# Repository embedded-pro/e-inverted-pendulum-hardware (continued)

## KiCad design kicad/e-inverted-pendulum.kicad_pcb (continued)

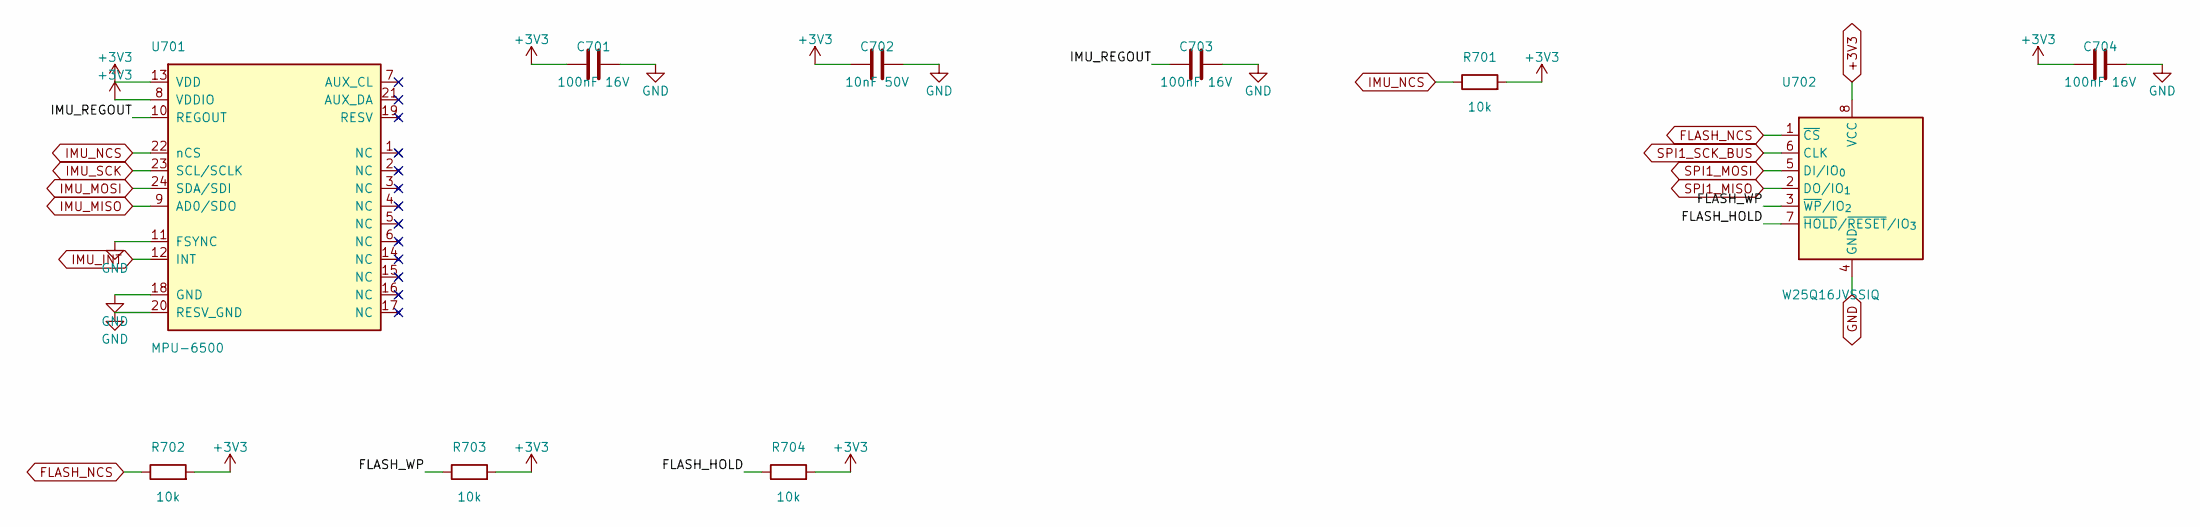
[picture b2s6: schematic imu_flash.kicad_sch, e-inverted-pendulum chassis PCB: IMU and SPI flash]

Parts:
C701, C703, C704: 100nF 16V; C_0402_1005Metric; MPN CL05B104KO5NNNC; LCSC C1525
C702: 10nF 50V; C_0603_1608Metric; MPN CL10B103KB8NNNC; LCSC C1589
R701, R702, R703, R704: 10k; R_0603_1608Metric; MPN 0603WAF1002T5E; LCSC C25804
U701: MPU-6500; InvenSense_QFN-24_3x3mm_P0.4mm; MPN MPU-6500; LCSC C50278
U702: W25Q16JVSSIQ; SOIC-8_5.3x5.3mm_P1.27mm; MPN W25Q16JVSSIQ; LCSC C131025

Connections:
+3V3: C701.1, C702.1, C704.1, R701.2, R702.2, R703.2, R704.2, U701.8 (VDDIO), U701.13 (VDD), U702.8 (VCC); also elsewhere on the board
/7 IMU and SPI flash/FLASH_HOLD: R704.1, U702.7 (~HOLD/~RESET/IO_{3})
/7 IMU and SPI flash/FLASH_WP: R703.1, U702.3 (~WP/IO_{2})
/7 IMU and SPI flash/IMU_REGOUT: C703.1, U701.10 (REGOUT)
FLASH_NCS: R702.1, U702.1 (~CS); also elsewhere on the board
GND: C701.2, C702.2, C703.2, C704.2, U701.11 (FSYNC), U701.18 (GND), U701.20 (RESV_GND), U702.4 (GND); also elsewhere on the board
IMU_INT: U701.12 (INT); also elsewhere on the board
IMU_MISO: U701.9 (AD0/SDO); also elsewhere on the board
IMU_MOSI: U701.24 (SDA/SDI); also elsewhere on the board
IMU_NCS: R701.1, U701.22 (nCS); also elsewhere on the board
IMU_SCK: U701.23 (SCL/SCLK); also elsewhere on the board
SPI1_MISO: U702.2 (DO/IO_{1}); also elsewhere on the board
SPI1_MOSI: U702.5 (DI/IO_{0}); also elsewhere on the board
SPI1_SCK_BUS: U702.6 (CLK); also elsewhere on the board

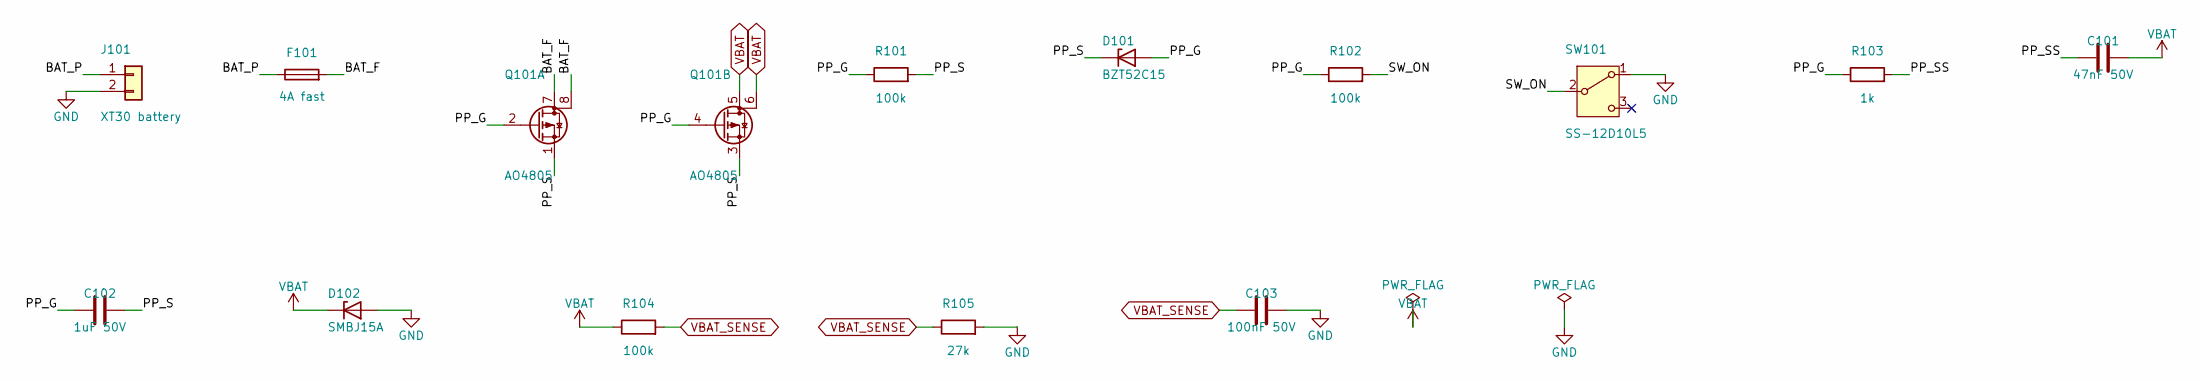
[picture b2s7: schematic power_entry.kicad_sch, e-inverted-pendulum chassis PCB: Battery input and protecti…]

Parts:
C101: 47nF 50V; C_0603_1608Metric; MPN CL10B473KB8NNNC; LCSC C1622
C102: 1uF 50V; C_0603_1608Metric; MPN CL10A105KB8NNNC; LCSC C15849
C103: 100nF 50V; C_0603_1608Metric; MPN CC0603KRX7R9BB104; LCSC C14663
D101: BZT52C15; D_SOD-123; MPN BZT52C15; LCSC C2104
D102: SMBJ15A; D_SMB; MPN SMBJ15A; LCSC C83846
F101: 4A fast; Fuse_1206_3216Metric; MPN 1206FA-4A; LCSC C2937379
J101: XT30 battery; AMASS_XT30UPB-F_1x02_P5.00mm_Vertical; MPN XT30UPB-F30.G.Y; LCSC C108769
Q101: AO4805; SOIC-8_3.9x4.9mm_P1.27mm; MPN AO4805; LCSC C3040596
R101, R102, R104: 100k; R_0603_1608Metric; MPN 0603WAF1003T5E; LCSC C25803
R103: 1k; R_0603_1608Metric; MPN 0603WAF1001T5E; LCSC C21190
R105: 27k; R_0603_1608Metric; MPN 0603WAF2702T5E; LCSC C22967
SW101: SS-12D10L5; SW_Slide_SPDT_SS-12D10L5_P4.70mm; MPN SS-12D10L5; LCSC C319012

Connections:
/1 Battery input and protection/BAT_F: F101.2, Q101.7 (D), Q101.8 (D)
/1 Battery input and protection/BAT_P: F101.1, J101.1
/1 Battery input and protection/PP_G: C102.1, D101.2 (A), Q101.2 (G), Q101.4 (G), R101.1, R102.1, R103.1
/1 Battery input and protection/PP_S: C102.2, D101.1 (K), Q101.1 (S), Q101.3 (S), R101.2
/1 Battery input and protection/PP_SS: C101.1, R103.2
/1 Battery input and protection/SW_ON: R102.2, SW101.2 (B)
GND: C103.2, D102.2 (A), J101.2, R105.2, SW101.1 (A); also elsewhere on the board
VBAT: C101.2, D102.1 (K), Q101.5 (D), Q101.6 (D), R104.1; also elsewhere on the board
VBAT_SENSE: C103.1, R104.2, R105.1; also elsewhere on the board

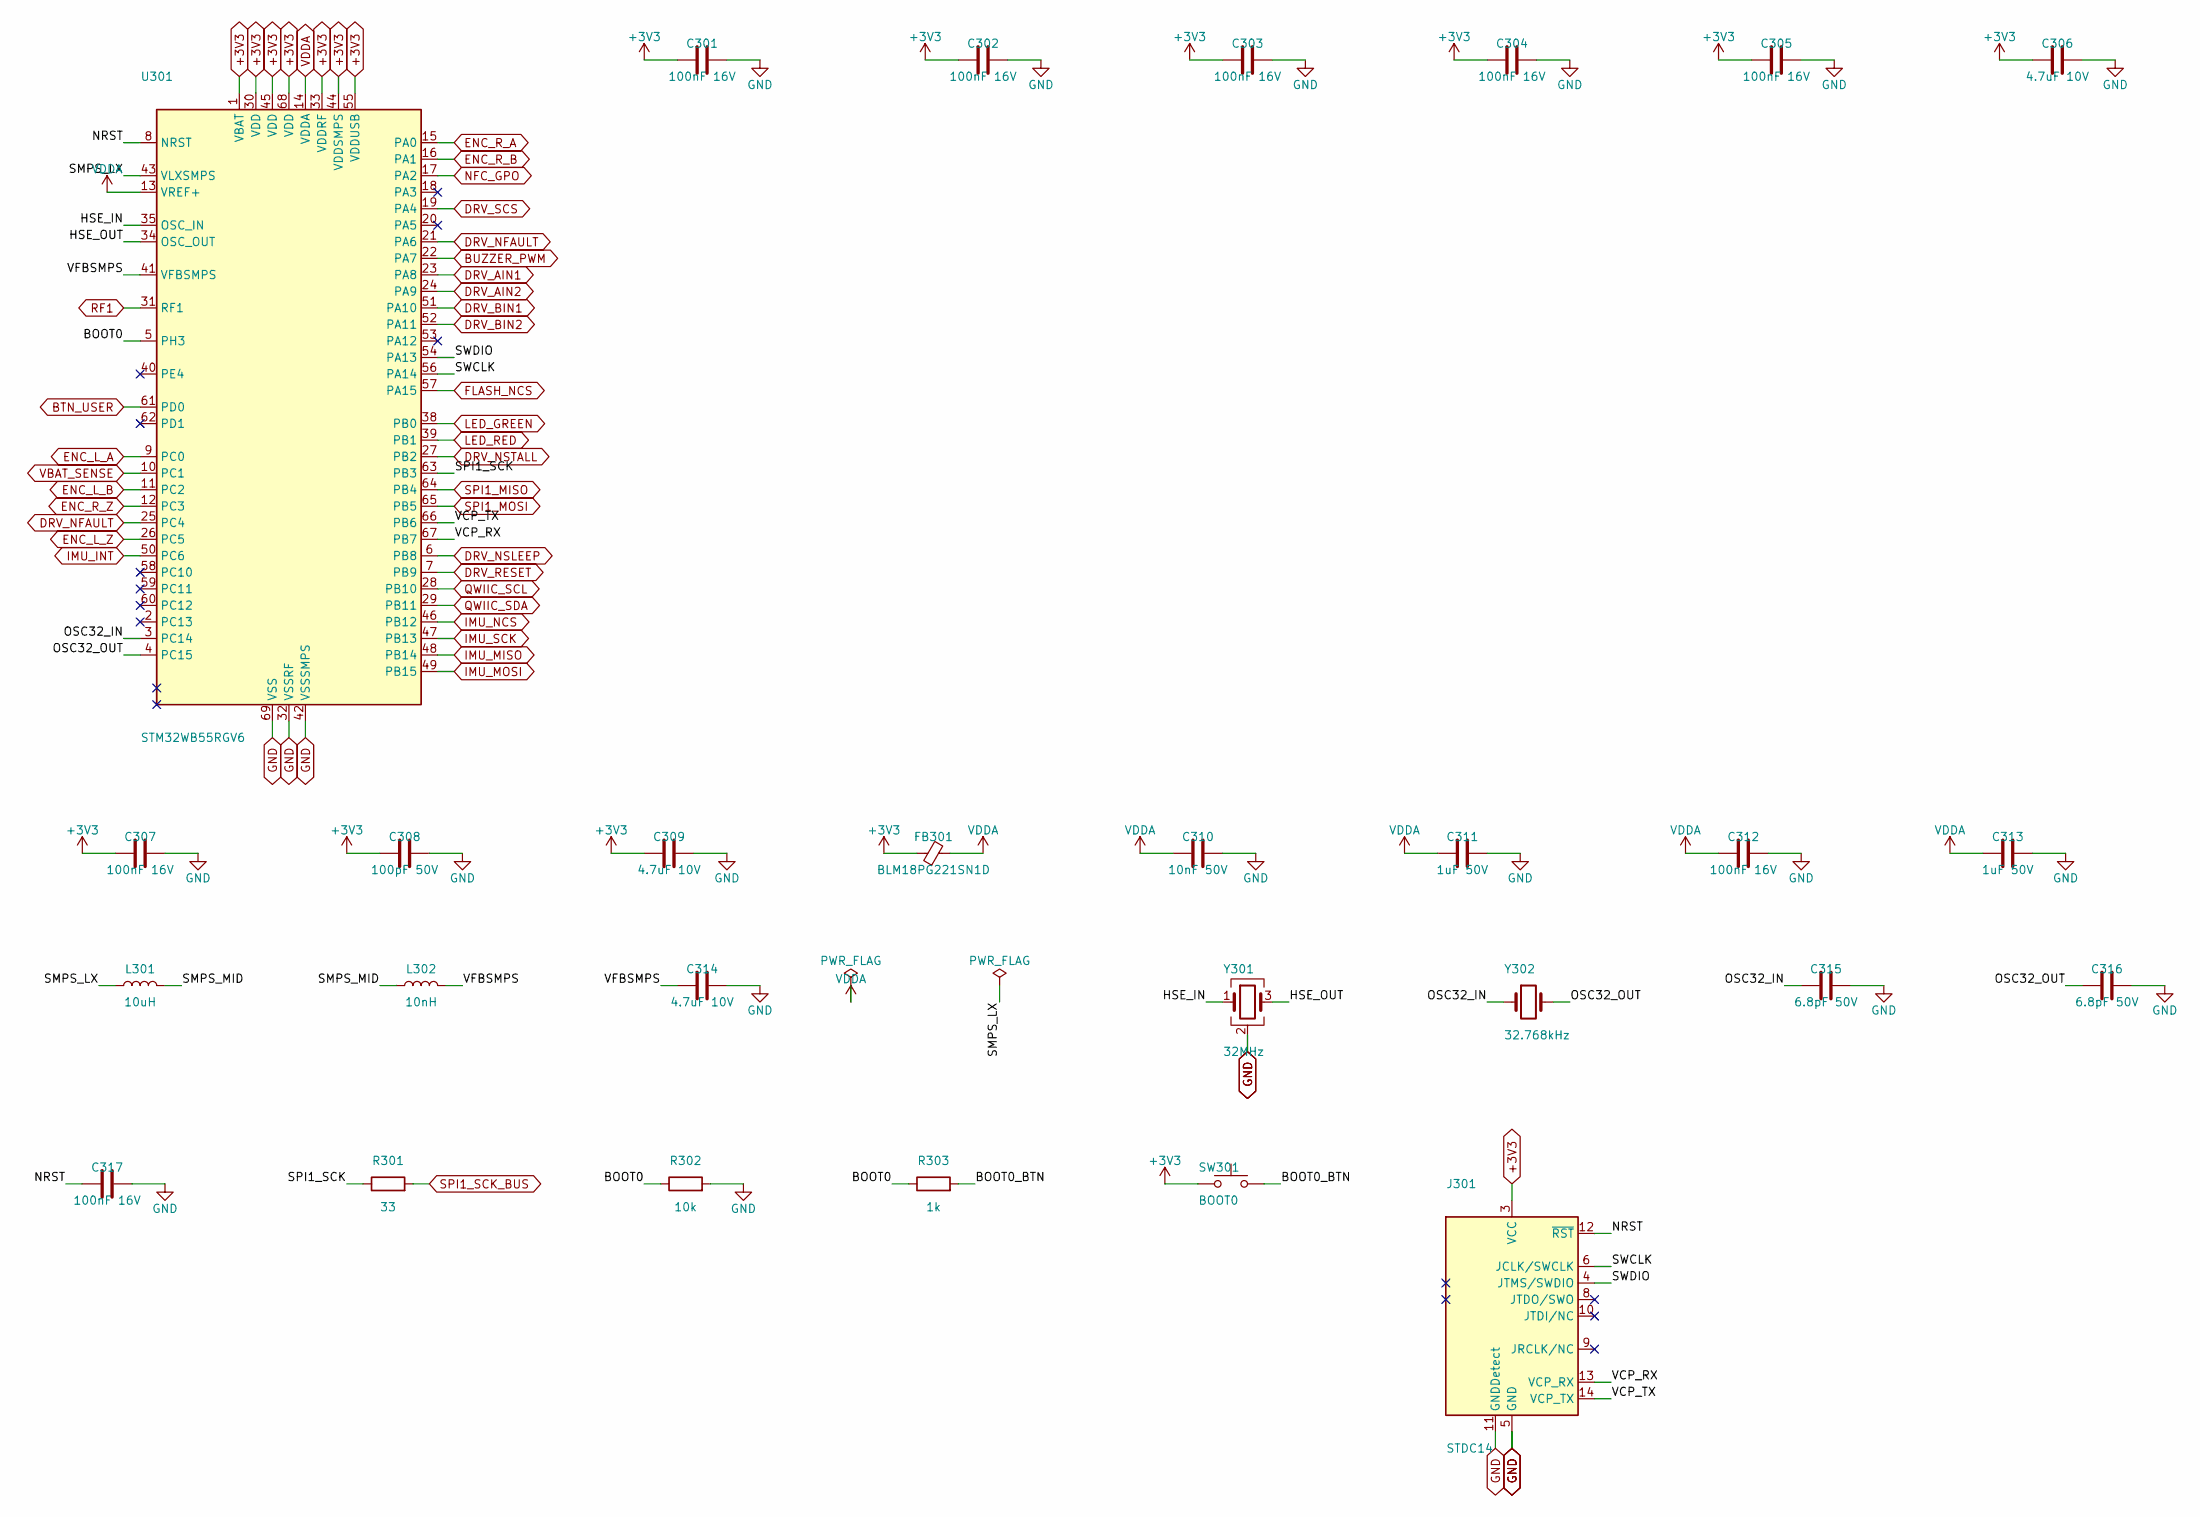
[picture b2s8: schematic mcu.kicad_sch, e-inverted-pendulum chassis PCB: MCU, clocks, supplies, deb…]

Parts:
C301, C302, C303, C304, C305, C307, C312, C317: 100nF 16V; C_0402_1005Metric; MPN CL05B104KO5NNNC; LCSC C1525
C306, C309, C314: 4.7uF 10V; C_0402_1005Metric; MPN CL05A475MP5NRNC; LCSC C23733
C308: 100pF 50V; C_0402_1005Metric; MPN CL05C101JB5NNNC; LCSC C26409
C310: 10nF 50V; C_0603_1608Metric; MPN CL10B103KB8NNNC; LCSC C1589
C311, C313: 1uF 50V; C_0603_1608Metric; MPN CL10A105KB8NNNC; LCSC C15849
C315, C316: 6.8pF 50V; C_0402_1005Metric; MPN CL05C6R8CB5NNNC; LCSC C318598
FB301: BLM18PG221SN1D; L_0603_1608Metric; MPN BLM18PG221SN1D; LCSC C80165
J301: STDC14; PinHeader_2x07_P1.27mm_Vertical_SMD; MPN FTSH-107-01-L-DV-K; LCSC C5307809
L301: 10uH; L_0805_2012Metric; MPN LQM21FN100M80L; LCSC C162582
L302: 10nH; L_0402_1005Metric; MPN LQG15HS10NJ02D; LCSC C77103
R301: 33; R_0603_1608Metric; MPN 0603WAF330JT5E; LCSC C23140
R302: 10k; R_0603_1608Metric; MPN 0603WAF1002T5E; LCSC C25804
R303: 1k; R_0603_1608Metric; MPN 0603WAF1001T5E; LCSC C21190
SW301: BOOT0; SW_Push_TS-1187A_5.1x5.1mm; MPN TS-1187A-B-A-B; LCSC C318884
U301: STM32WB55RGV6; QFN-68-1EP_8x8mm_P0.4mm_EP6.4x6.4mm; MPN STM32WB55RGV6; LCSC C401505
Y301: 32MHz; Crystal_SMD_2016-4Pin_2.0x1.6mm; MPN NX2016SA-32MHZ-EXS00A-CS06654; LCSC C5441424
Y302: 32.768kHz; Crystal_SMD_3215-2Pin_3.2x1.5mm; MPN NX3215SA-32.768K-STD-MUA-14; LCSC C156244

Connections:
+3V3: C301.1, C302.1, C303.1, C304.1, C305.1, C306.1, C307.1, C308.1, C309.1, FB301.1, J301.3 (VCC), SW301.1, U301.1 (VBAT), U301.30 (VDD), U301.33 (VDDRF), U301.44 (VDDSMPS), U301.45 (VDD), U301.55 (VDDUSB), U301.68 (VDD); also elsewhere on the board
/3 MCU, clocks, supplies, debug/BOOT0: R302.1, R303.1, U301.5 (PH3)
/3 MCU, clocks, supplies, debug/BOOT0_BTN: R303.2, SW301.2
/3 MCU, clocks, supplies, debug/HSE_IN: U301.35 (OSC_IN), Y301.1
/3 MCU, clocks, supplies, debug/HSE_OUT: U301.34 (OSC_OUT), Y301.3
/3 MCU, clocks, supplies, debug/NRST: C317.1, J301.12 (~RST), U301.8 (NRST)
/3 MCU, clocks, supplies, debug/OSC32_IN: C315.1, U301.3 (PC14), Y302.1
/3 MCU, clocks, supplies, debug/OSC32_OUT: C316.1, U301.4 (PC15), Y302.2
/3 MCU, clocks, supplies, debug/SMPS_LX: L301.1, U301.43 (VLXSMPS)
/3 MCU, clocks, supplies, debug/SMPS_MID: L301.2, L302.1
/3 MCU, clocks, supplies, debug/SPI1_SCK: R301.1, U301.63 (PB3)
/3 MCU, clocks, supplies, debug/SWCLK: J301.6 (JCLK/SWCLK), U301.56 (PA14)
/3 MCU, clocks, supplies, debug/SWDIO: J301.4 (JTMS/SWDIO), U301.54 (PA13)
/3 MCU, clocks, supplies, debug/VCP_RX: J301.13 (VCP_RX), U301.67 (PB7)
/3 MCU, clocks, supplies, debug/VCP_TX: J301.14 (VCP_TX), U301.66 (PB6)
/3 MCU, clocks, supplies, debug/VFBSMPS: C314.1, L302.2, U301.41 (VFBSMPS)
BTN_USER: U301.61 (PD0); also elsewhere on the board
BUZZER_PWM: U301.22 (PA7); also elsewhere on the board
DRV_AIN1: U301.23 (PA8); also elsewhere on the board
DRV_AIN2: U301.24 (PA9); also elsewhere on the board
DRV_BIN1: U301.51 (PA10); also elsewhere on the board
DRV_BIN2: U301.52 (PA11); also elsewhere on the board
DRV_NFAULT: U301.21 (PA6), U301.25 (PC4); also elsewhere on the board
DRV_NSLEEP: U301.6 (PB8); also elsewhere on the board
DRV_NSTALL: U301.27 (PB2); also elsewhere on the board
DRV_RESET: U301.7 (PB9); also elsewhere on the board
DRV_SCS: U301.19 (PA4); also elsewhere on the board
ENC_L_A: U301.9 (PC0); also elsewhere on the board
ENC_L_B: U301.11 (PC2); also elsewhere on the board
ENC_L_Z: U301.26 (PC5); also elsewhere on the board
ENC_R_A: U301.15 (PA0); also elsewhere on the board
ENC_R_B: U301.16 (PA1); also elsewhere on the board
ENC_R_Z: U301.12 (PC3); also elsewhere on the board
FLASH_NCS: U301.57 (PA15); also elsewhere on the board
GND: C301.2, C302.2, C303.2, C304.2, C305.2, C306.2, C307.2, C308.2, C309.2, C310.2, C311.2, C312.2, C313.2, C314.2, C315.2, C316.2, C317.2, J301.5 (GND), J301.7 (GND), J301.11 (GNDDetect), R302.2, U301.32 (VSSRF), U301.42 (VSSSMPS), U301.69 (VSS), Y301.2 (G), Y301.4 (G); also elsewhere on the board
IMU_INT: U301.50 (PC6); also elsewhere on the board
IMU_MISO: U301.48 (PB14); also elsewhere on the board
IMU_MOSI: U301.49 (PB15); also elsewhere on the board
IMU_NCS: U301.46 (PB12); also elsewhere on the board
IMU_SCK: U301.47 (PB13); also elsewhere on the board
LED_GREEN: U301.38 (PB0); also elsewhere on the board
LED_RED: U301.39 (PB1); also elsewhere on the board
NFC_GPO: U301.17 (PA2); also elsewhere on the board
QWIIC_SCL: U301.28 (PB10); also elsewhere on the board
QWIIC_SDA: U301.29 (PB11); also elsewhere on the board
RF1: U301.31 (RF1); also elsewhere on the board
SPI1_MISO: U301.64 (PB4); also elsewhere on the board
SPI1_MOSI: U301.65 (PB5); also elsewhere on the board
SPI1_SCK_BUS: R301.2; also elsewhere on the board
VBAT_SENSE: U301.10 (PC1); also elsewhere on the board
VDDA: C310.1, C311.1, C312.1, C313.1, FB301.2, U301.13 (VREF+), U301.14 (VDDA)

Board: 4 copper layers, 189 parts (0 on the bottom side), 122 nets, no tracks yet.

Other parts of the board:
MB1, MB2, MB3, MB4: bracket M3; MountingHole_M3_NPTH_KeepOut7mm
MB5, MB6, MB7, MB8: bracket M2; MountingHole_M2_NPTH_KeepOut5.5mm
MC1, MC2, MC3, MC4: battery cradle; MountingHole_M3_NPTH_KeepOut7mm
MH1: bumper; MountingHole_M3_NPTH_KeepOut7mm
MH2: bumper (nylon); MountingHole_M3_NPTH_KeepOut7mm

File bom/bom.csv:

group,function,mpn,lcsc,qty,notes
schematic,MLT-8530,MLT-8530,C94599,1,BZ801
schematic,47nF 50V,CL10B473KB8NNNC,C1622,2,"C101,C205"
schematic,1uF 50V,CL10A105KB8NNNC,C15849,6,"C102,C209,C311,C313,C509,C512"
schematic,100nF 50V,CC0603KRX7R9BB104,C14663,8,"C103,C203,C208,C503,C506,C510,C602,C801"
schematic,10uF 25V,CL21A106KAYNNNE,C15850,4,"C201,C202,C502,C505"
schematic,100nF 16V,CL05B104KO5NNNC,C1525,17,"C204,C301,C302,C303,C304,C305,C307,C312,C317,C511,C606,C610,C701,C703,C704,C802,C803"
schematic,22uF 25V,CL21A226MAQNNNE,C45783,2,"C206,C207"
schematic,2.2uF 25V,CL10A225KO8NNNC,C23630,1,C210
schematic,4.7uF 10V,CL05A475MP5NRNC,C23733,3,"C306,C309,C314"
schematic,100pF 50V,CL05C101JB5NNNC,C26409,1,C308
schematic,10nF 50V,CL10B103KB8NNNC,C1589,3,"C310,C508,C702"
schematic,6.8pF 50V,CL05C6R8CB5NNNC,C318598,2,"C315,C316"
schematic,220u 35V,EEEFK1V221P,C178562,1,C507
schematic,1nF 50V,CL05C102JB5NNNC,C307441,1,C513
schematic,10uF 10V,CL10A106KP8NNNC,C19702,1,C601
schematic,1nF 50V,CL10B102KB8NNNC,C1588,4,"C604,C605,C608,C609"
schematic,BZT52C15,BZT52C15,C2104,1,D101
schematic,SMBJ15A,SMBJ15A,C83846,1,D102
schematic,SS34,SS34,C8678,4,"D501,D502,D503,D504"
schematic,green,KT-0603G,C12624,1,D801
schematic,red,KT-0603R,C2286,1,D802
schematic,1N4148WS,1N4148WS,C2128,1,D803
schematic,4A fast,1206FA-4A,C2937379,1,F101
schematic,PTC 100mA,SMD0805P010TF,C20975,1,F601
schematic,BLM18PG221SN1D,BLM18PG221SN1D,C80165,1,FB301
schematic,MLPF-WB55-01E3,MLPF-WB55-01E3,C2651048,1,FL401
schematic,XT30 battery,XT30UPB-F30.G.Y,C108769,1,J101
schematic,STDC14,FTSH-107-01-L-DV-K,C5307809,1,J301
schematic,"Motor left,Motor right",S6B-PH-K-S(LF)(SN),C157920,2,"J601,J602"
schematic,Qwiic,SM04B-SRSS-TB(LF)(SN),C160404,1,J801
schematic,4.7uH,SWPA4030S4R7MT,C57269,1,L201
schematic,10uH,LQM21FN100M80L,C162582,1,L301
schematic,10nH,LQG15HS10NJ02D,C77103,1,L302
schematic,AO4805,AO4805,C3040596,1,Q101
schematic,CSD88537ND,CSD88537ND,C117439,4,"Q501,Q502,Q503,Q504"
schematic,MMBT3904,MMBT3904,C20526,1,Q801
schematic,100k,0603WAF1003T5E,C25803,3,"R101,R102,R104"
schematic,1k,0603WAF1001T5E,C21190,2,"R103,R303"
schematic,27k,0603WAF2702T5E,C22967,1,R105
schematic,240k,0603WAF2403T5E,C4197,1,R201
schematic,36k,0603WAF3602T5E,C23147,1,R202
schematic,52.3k,0603WAF5232T5E,C23198,1,R203
schematic,10k,0603WAF1002T5E,C25804,12,"R204,R302,R515,R516,R518,R701,R702,R703,R704,R803,R807,R810"
schematic,33,0603WAF330JT5E,C23140,2,"R301,R805"
schematic,0,0402WGF0000TCE,C17168,1,R401
schematic,0,0603WAF0000T5E,C21189,13,"R501,R502,R503,R504,R505,R506,R507,R508,R510,R511,R513,R514,R601"
schematic,50m,HoLR1206-1W-50mR-1%-75ppm,C601102,2,"R509,R512"
schematic,2.2k,0603WAF2201T5E,C4190,3,"R517,R808,R809"
schematic,100,0603WAF1000T5E,C22775,5,"R604,R606,R608,R610,R804"
schematic,470,0603WAF4700T5E,C23179,2,"R801,R806"
schematic,680,0603WAF6800T5E,C23228,1,R802
schematic,SS-12D10L5,SS-12D10L5,C319012,1,SW101
schematic,"BOOT0,USER",TS-1187A-B-A-B,C318884,2,"SW301,SW801"
schematic,TPS62933F,TPS62933FDRLR,C5219272,1,U201
schematic,TLV75533P,TLV75533PDBVR,C404027,1,U202
schematic,STM32WB55RGV6,STM32WB55RGV6,C401505,1,U301
schematic,DRV8711,DRV8711DCPR,C60013,1,U501
schematic,TPD4E05U06DQAR,TPD4E05U06DQAR,C138714,3,"U601,U603,U801"
schematic,SN74LVC3G17DCTR,SN74LVC3G17DCTR,C18213,2,"U602,U604"
schematic,MPU-6500,MPU-6500,C50278,1,U701
schematic,W25Q16JVSSIQ,W25Q16JVSSIQ,C131025,1,U702
schematic,M24C64-RMN6TP,M24C64-RMN6TP,C79988,1,U802
schematic,ST25DV04KC-IE8S3,ST25DV04KC-IE8S3,C5221752,1,U803
schematic,32MHz,NX2016SA-32MHZ-EXS00A-CS06654,C5441424,1,Y301
schematic,32.768kHz,NX3215SA-32.768K-STD-MUA-14,C156244,1,Y302
